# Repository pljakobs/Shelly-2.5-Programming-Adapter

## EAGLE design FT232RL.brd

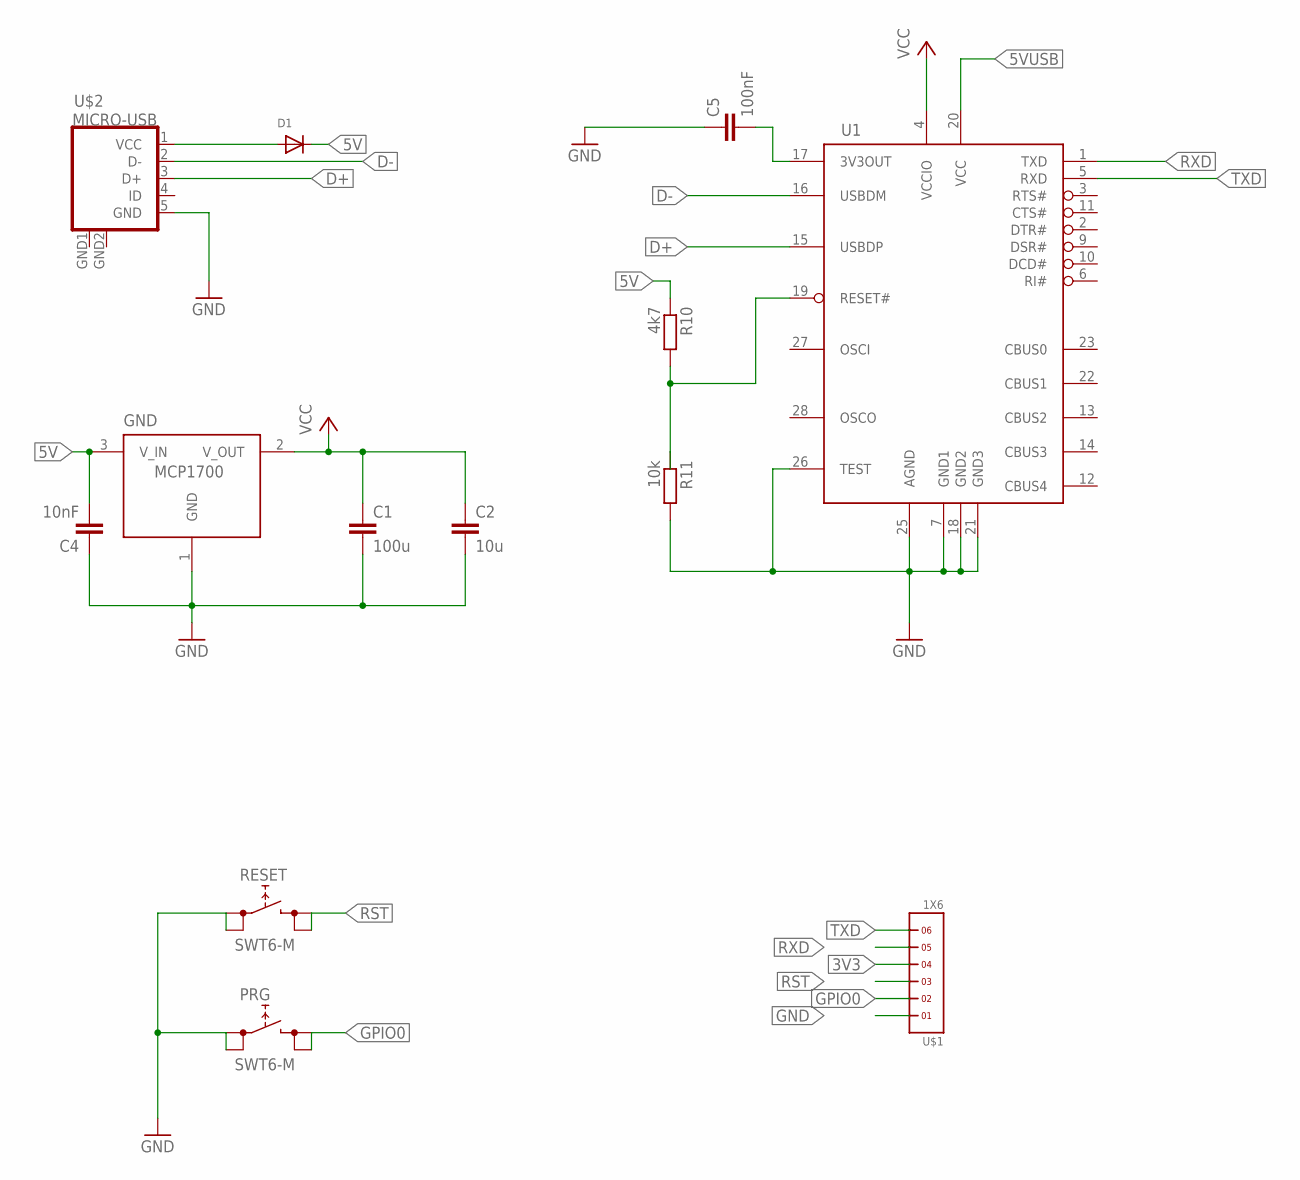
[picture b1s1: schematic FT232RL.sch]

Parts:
C1: 100u; C0805
C2: 10u; C0805
C4: 10nF; C0805
C5: 100nF; C0805
D1: DIODESOD-323F; SOD-323F
GND: MCP1700SOT23; SOT-23
PRG: SWT6-M
R10: 4k7; R0603
R11: 10k; R0603
RESET: SWT6-M
U1: FT232RL; SSOP28DB
U$1: 1X6
U$2: MICRO-USB

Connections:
3V3: C1.1, C2.1, GND.2 (V_OUT), U1.4 (VCCIO), U$1.4
3V3OUT: C5.2, U1.17 (3V3OUT)
5V: C4.2, D1.C, GND.3 (V_IN), R10.1, U1.20 (VCC)
5VUSB: D1.A, U$2.1 (VCC)
D+: U1.15 (USBDP), U$2.3 (D+)
D-: U1.16 (USBDM), U$2.2 (D-)
GND: C1.2, C2.2, C4.1, C5.1, GND.1 (GND), PRG.1 (0), PRG.2 (0), R11.2, RESET.1 (0), RESET.2 (0), U1.7 (GND1), U1.18 (GND2), U1.21 (GND3), U1.25 (AGND), U1.26 (TEST), U$1.1, U$2.5 (GND), U$2.GND1 (GND), U$2.GND2 (GND)
GPIO0: PRG.3 (1), PRG.4 (1), U$1.2
RESET: R10.2, R11.1, U1.19 (RESET#)
RST: RESET.3 (1), RESET.4 (1), U$1.3
RXD: U1.1 (TXD), U$1.5
TXD: U1.5 (RXD), U$1.6

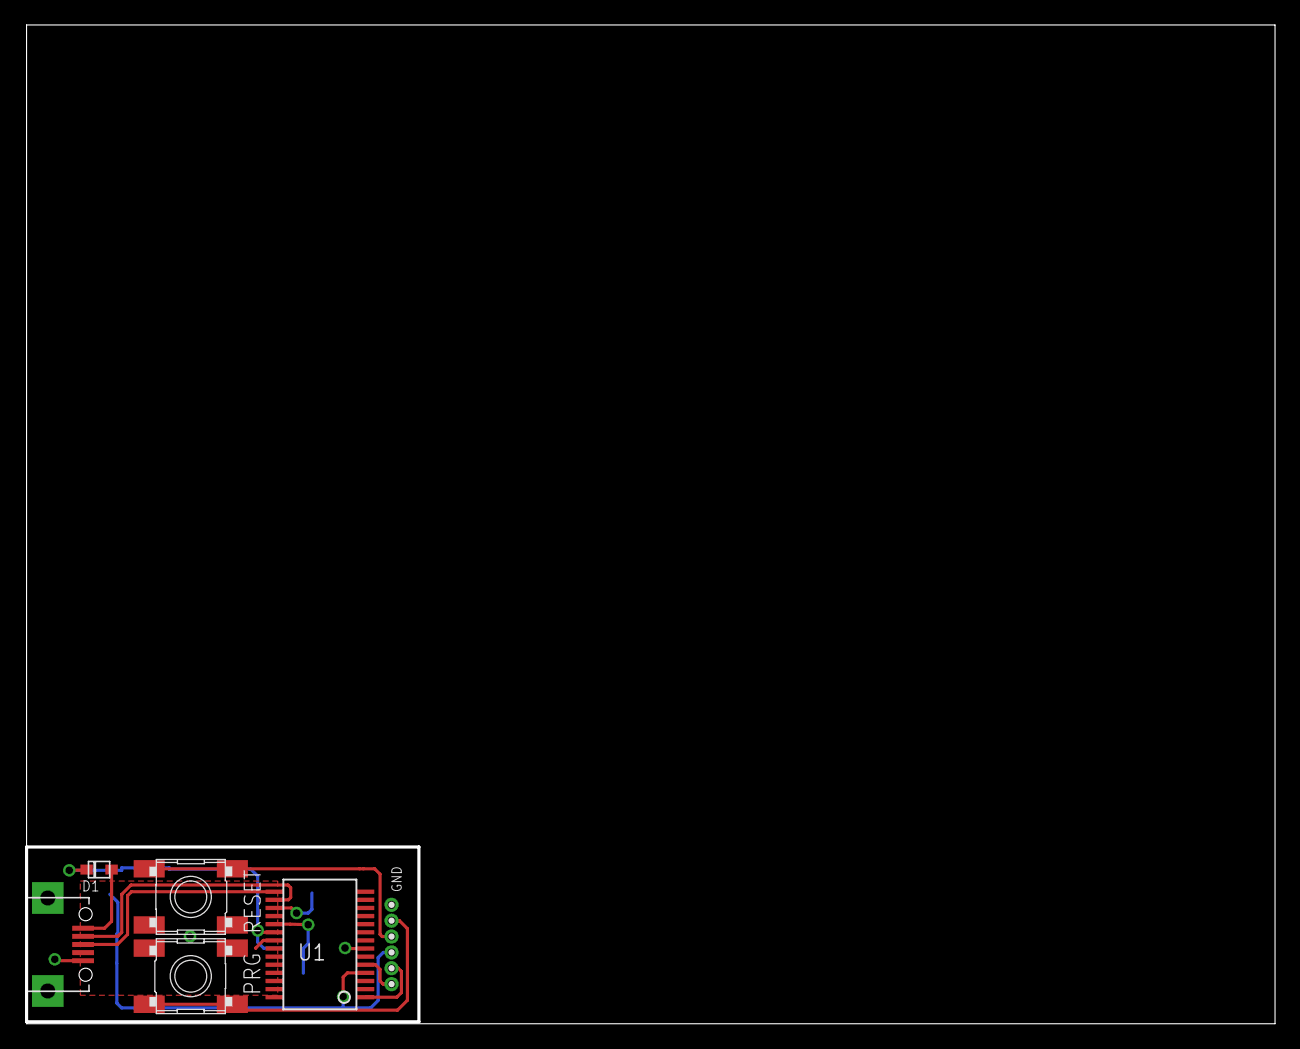
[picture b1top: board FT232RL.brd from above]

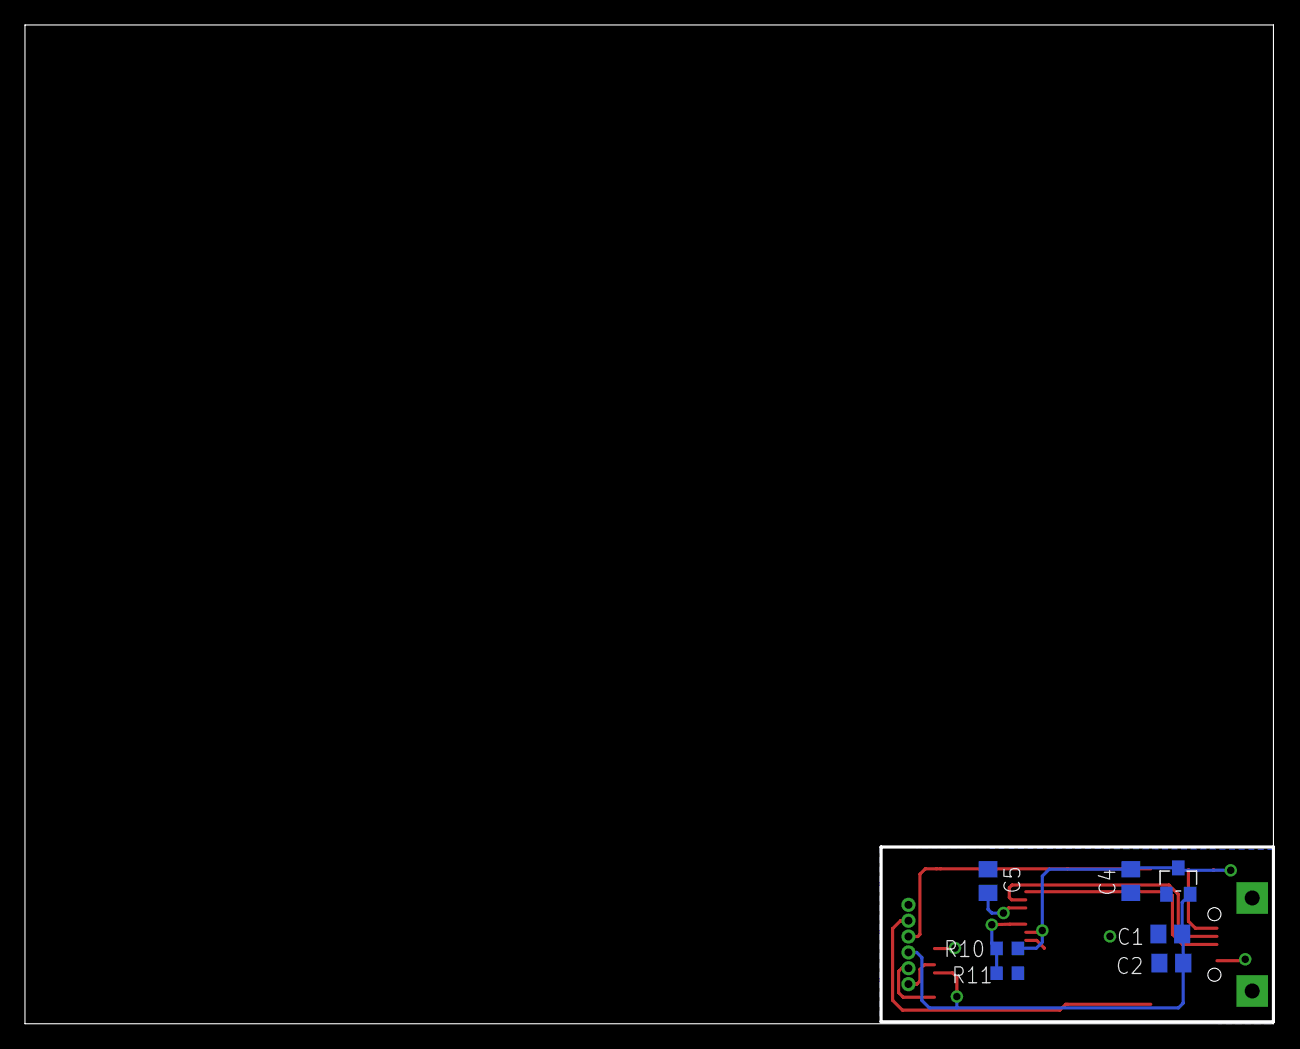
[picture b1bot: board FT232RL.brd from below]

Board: 2 copper layers, 100.0 x 80.0 mm, 13 parts (7 on the bottom side), 12 nets.
